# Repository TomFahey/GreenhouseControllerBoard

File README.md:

# Greenhouse Controller Board
Greenhouse irrigation control and sensor board, based on the ESP32 microcontroller and designed with Autodesk Eagle.

A simple 2-layer PCB design for an irrigation controller, designed to control up to four 12V solenoid valve water valves, 
based on temperature, humidity and other arbitrary parameters.

Based on Espressif's popular ESP32 microncontroller, this controller board incorporates a number of features, including:

- Flexible Wi-Fi/Bluetooth control, tracking and automation of plants through open-source Arduino libraries (also compatible with ESPHome)
- Individual control for up to four DC solenoid valves via 2.1mm x 5.5mm barrel jack, with LED status indicators
- 12V DC power input, built-in 3.3V voltage regulation for microcontroller and peripherals, up to 4A load
- High precision temperature, pressure and humidity sensing, using Bosch's BME280 MEMS sensor
- Up to 8 individual 12-bit ADC channels for additional environmental monitoring, such as soil moisture sensors
- An additional 4 GPIO channels, and two I2C connectors for further expansion e.g LED strips (separate power supply required)

Some renders from Fusion 360:

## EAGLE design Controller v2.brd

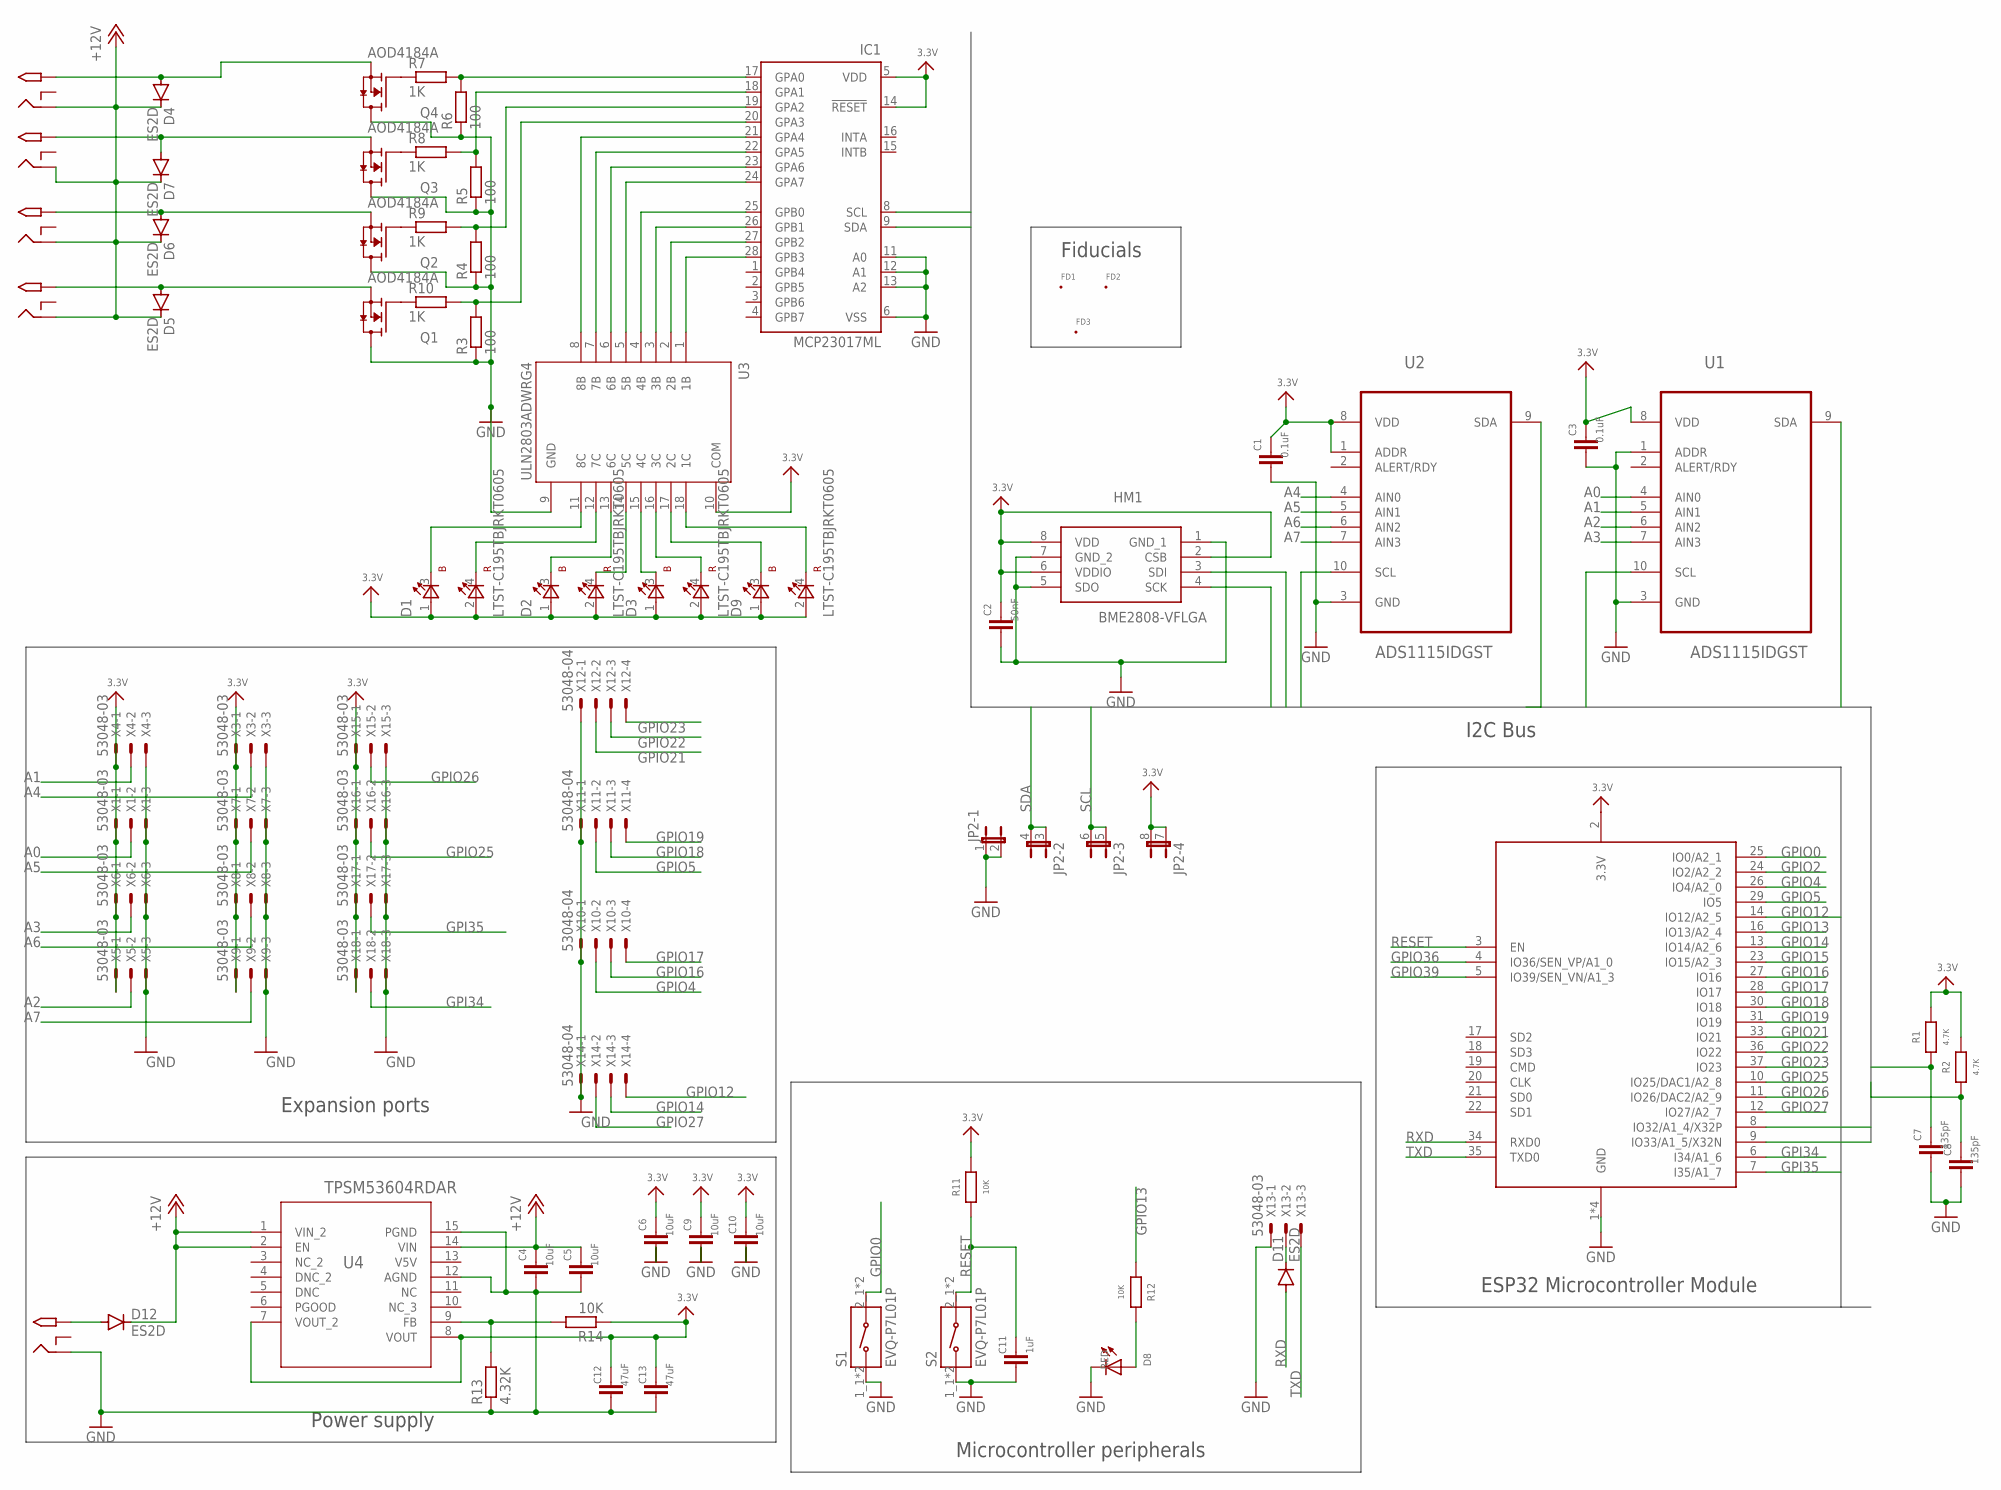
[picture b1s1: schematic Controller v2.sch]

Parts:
12V_OUT_A, 12V_OUT_B, 12V_OUT_C, 12V_OUT_D: 2.1MMJACKTHM; PJ-102A
C1, C3: 0.1uF; C0603
C2: 50nF; C0603
C4, C5, C6, C9, C10: 10uF; C0805K
C7, C8: 135pF; C0603
C11: 1uF; C0805K
C12, C13: 47uF; C0805K
D1, D2, D3, D9: LTST-C195TBJRKT0605; LED_LTST-C195TBJRKT
D4, D5, D6, D7, D11, D12: ES2D; SMB; MPN ES2D; DIGI-KEY-PART-NUMBER ES2DFSCT-ND
D8: RED; CHIPLED_0805
FD1, FD2, FD3: FID_20MIL; FID_020
HM1: BME2808-VFLGA; BME280
IC1: MCP23017ML; QFN28-ML_6X6MM
JP2: 3.3V; JP4Q
PWRIN: 2.1MMJACKTHM; PJ-102A
Q1, Q2, Q3, Q4: AOD4184A; D-PAK_TO252AA
R1, R2: 4.7K; R0805
R3, R4, R5, R6: 100; R0402
R7, R8, R9, R10: 1K; R0402
R11: 10K; R0603
R12: 10K; R0805
R13: 4.32K; R0402
R14: 10K; R0402
S1, S2: EVQ-P7L01P; SW_EVQ-P7L01P
U1, U2: ADS1115IDGST; SOP50P490X110-10N
U3: ULN2803ADWRG4; SOIC127P1030X265-18N
U4: TPSM53604RDAR; B3QFN14_RDA_TEX
X1, X3, X4, X5, X6, X7, X8, X9, X13, X15, X16, X17, X18: 53048-03
X2: ESP32_WROOM32; WROOM32; MPN N/A
X10, X11, X12, X14: 53048-04

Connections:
3.3V: C1.1, C2.1, C3.1, C6.1, C9.1, C10.1, C12.1, C13.1, D1.1 (A1), D1.2 (A2), D2.1 (A1), D2.2 (A2), D3.1 (A1), D3.2 (A2), D9.1 (A1), D9.2 (A2), HM1.2 (CSB), HM1.6 (VDDIO), HM1.8 (VDD), IC1.5 (VDD), IC1.14 (!RESET), JP2.7 (1), JP2.8 (2), R1.2, R2.2, R11.2, R14.1, U1.8 (VDD), U2.1 (ADDR), U2.8 (VDD), U3.10 (COM), U4.7 (VOUT_2), U4.8 (VOUT), X1.1, X2.2 (3.3V), X3.1, X4.1, X5.1, X6.1, X7.1, X8.1, X9.1, X15.1, X16.1, X17.1, X18.1
+12V: 12V_OUT_A.RING, 12V_OUT_B.RING, 12V_OUT_C.RING, 12V_OUT_D.RING, C4.1, C5.1, D4.C, D5.C, D6.C, D7.C, D12.C, U4.1 (VIN_2), U4.2 (EN), U4.14 (VIN)
A0: U1.4 (AIN0), X1.2
A1: U1.5 (AIN1), X4.2
A2: U1.6 (AIN2), X5.2
A3: U1.7 (AIN3), X6.2
A4: U2.4 (AIN0), X3.2
A5: U2.5 (AIN1), X7.2
A6: U2.6 (AIN2), X8.2
A7: U2.7 (AIN3), X9.2
GND: C1.2, C2.2, C3.2, C4.2, C5.2, C6.2, C7.2, C8.2, C9.2, C10.2, C11.2, C12.2, C13.2, D8.C, HM1.1 (GND_1), HM1.5 (SDO), HM1.7 (GND_2), IC1.6 (VSS), IC1.11 (A0), IC1.12 (A1), IC1.13 (A2), JP2.1, JP2.2, PWRIN.RING, Q1.4 (D), Q2.4 (D), Q3.4 (D), Q4.4 (D), R3.1, R4.1, R5.1, R6.1, R13.1, S1.1_1 (1), S1.1_2 (1), S2.1_1 (1), S2.1_2 (1), U1.1 (ADDR), U1.3 (GND), U2.3 (GND), U3.9 (GND), U4.12 (AGND), U4.15 (PGND), X1.3, X2.1 (GND), X2.15 (GND), X2.38 (GND), X2.P$1 (GND), X3.3, X4.3, X5.3, X6.3, X7.3, X8.3, X9.3, X10.1, X11.1, X12.1, X13.1, X14.1, X15.3, X16.3, X17.3, X18.3
GPI34: X2.6 (I34/A1_6), X18.2
GPI35: X2.7 (I35/A1_7), X17.2
GPIO0: S1.2_1 (2), S1.2_2 (2), X2.25 (IO0/A2_1)
GPIO2: X2.24 (IO2/A2_2)
GPIO4: X2.26 (IO4/A2_0), X10.2
GPIO5: X2.29 (IO5), X11.2
GPIO12: X2.14 (IO12/A2_5), X14.4
GPIO13: R12.1, X2.16 (IO13/A2_4)
GPIO14: X2.13 (IO14/A2_6), X14.3
GPIO15: X2.23 (IO15/A2_3)
GPIO16: X2.27 (IO16), X10.3
GPIO17: X2.28 (IO17), X10.4
GPIO18: X2.30 (IO18), X11.3
GPIO19: X2.31 (IO19), X11.4
GPIO21: X2.33 (IO21), X12.2
GPIO22: X2.36 (IO22), X12.3
GPIO23: X2.37 (IO23), X12.4
GPIO25: X2.10 (IO25/DAC1/A2_8), X16.2
GPIO26: X2.11 (IO26/DAC2/A2_9), X15.2
GPIO27: X2.12 (IO27/A2_7), X14.2
GPIO36: X2.4 (IO36/SEN_VP/A1_0)
GPIO39: X2.5 (IO39/SEN_VN/A1_3)
unnamed: IC1.17 (GPA0), R6.2, R7.2
unnamed: IC1.18 (GPA1), R5.2, R8.2
unnamed: IC1.20 (GPA3), R3.2, R10.2
unnamed: IC1.19 (GPA2), R4.2, R9.2
unnamed: Q1.1 (G), R10.1
unnamed: D12.A, PWRIN.TIP
unnamed: Q2.1 (G), R9.1
unnamed: IC1.21 (GPA4), U3.8 (8B)
unnamed: Q3.1 (G), R8.1
unnamed: Q4.1 (G), R7.1
unnamed: D11.C, X13.2
unnamed: IC1.22 (GPA5), U3.7 (7B)
unnamed: IC1.23 (GPA6), U3.6 (6B)
unnamed: IC1.24 (GPA7), U3.5 (5B)
unnamed: D8.A, R12.2
unnamed: IC1.25 (GPB0), U3.4 (4B)
unnamed: IC1.26 (GPB1), U3.3 (3B)
unnamed: IC1.27 (GPB2), U3.2 (2B)
unnamed: IC1.28 (GPB3), U3.1 (1B)
unnamed: D1.3 (K1), U3.11 (8C)
unnamed: D1.4 (K2), U3.12 (7C)
unnamed: D2.3 (K1), U3.13 (6C)
unnamed: D2.4 (K2), U3.14 (5C)
unnamed: D3.3 (K1), U3.15 (4C)
unnamed: D3.4 (K2), U3.16 (3C)
unnamed: D9.3 (K1), U3.17 (2C)
unnamed: D9.4 (K2), U3.18 (1C)
unnamed: R13.2, R14.2, U4.9 (FB)
RESET: C11.1, R11.1, S2.2_1 (2), S2.2_2 (2), X2.3 (EN)
RXD: D11.A, X2.34 (RXD0)
SCL: C7.1, HM1.4 (SCK), IC1.8 (SCL), JP2.5 (1), JP2.6 (2), R1.1, U1.10 (SCL), U2.10 (SCL), X2.9 (IO33/A1_5/X32N)
SDA: C8.1, HM1.3 (SDI), IC1.9 (SDA), JP2.3 (1), JP2.4 (2), R2.1, U1.9 (SDA), U2.9 (SDA), X2.8 (IO32/A1_4/X32P)
TXD: X2.35 (TXD0), X13.3
V_COL1: 12V_OUT_A.TIP, D4.A, Q4.3 (S)
V_COL2: 12V_OUT_B.TIP, D7.A, Q3.3 (S)
V_COL3: 12V_OUT_C.TIP, D6.A, Q2.3 (S)
V_COL4: 12V_OUT_D.TIP, D5.A, Q1.3 (S)

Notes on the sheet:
Fiducials
I2C Bus
Microcontroller peripherals
ESP32 Microcontroller Module
Power supply
Expansion ports

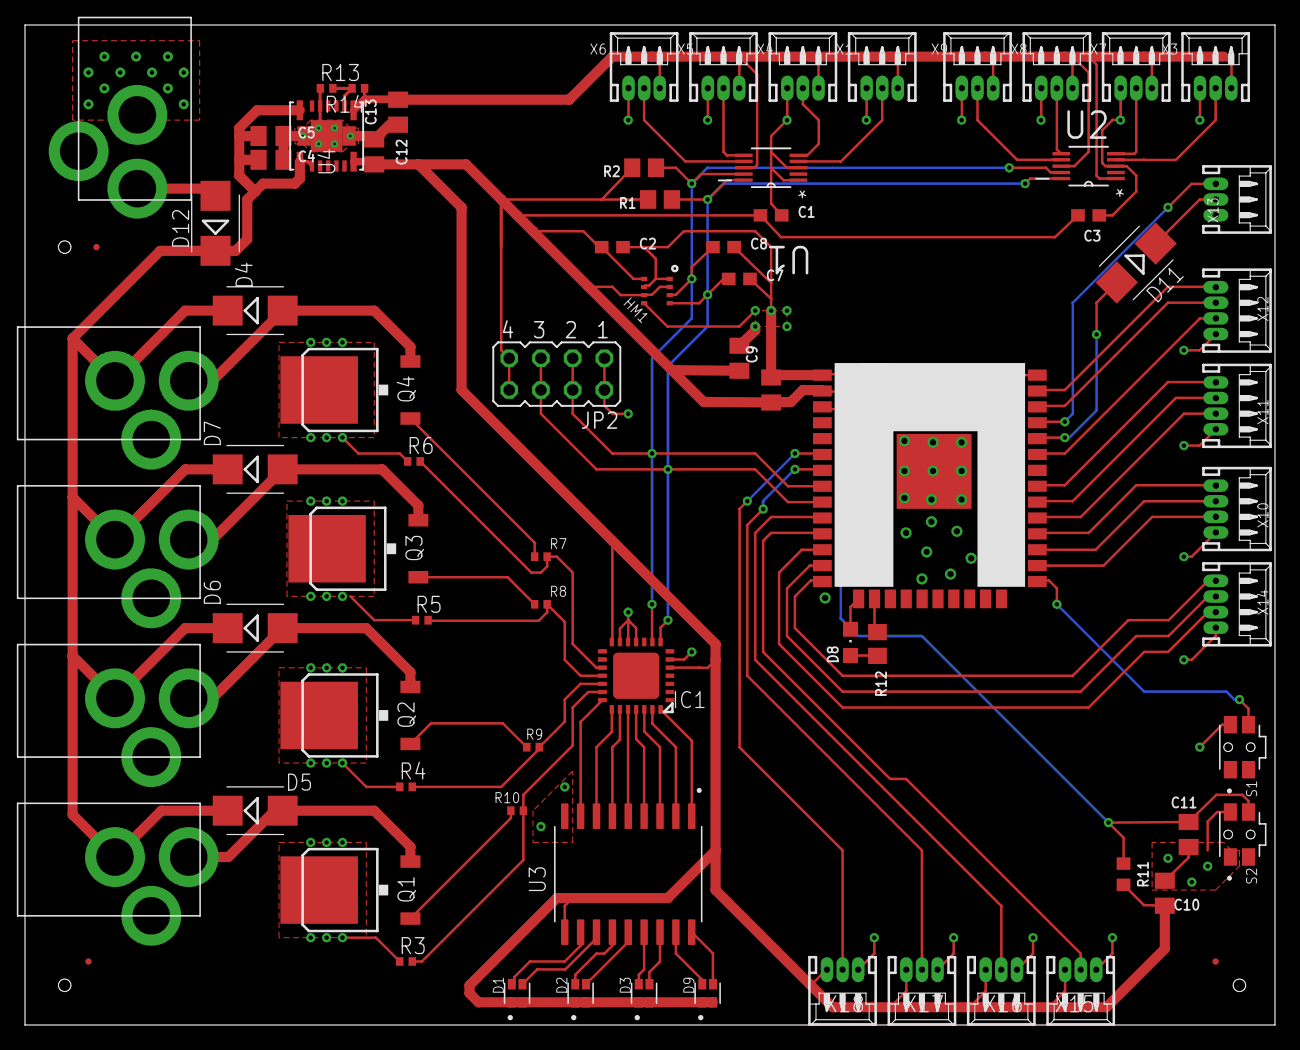
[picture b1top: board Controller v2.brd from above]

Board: 2 copper layers, 100.0 x 80.0 mm, 77 parts (0 on the bottom side), 66 nets.

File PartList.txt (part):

Partlist

Exported from Controller v2.sch at 12/07/2021 17:28

EAGLE Version 9.6.2 Copyright (c) 1988-2020 Autodesk, Inc.

Assembly variant: 

Part      Value               Device              Package              Library                                Sheet

12V_OUT_A 2.1MMJACKTHM        2.1MMJACKTHM        PJ-102A              adafruit                               1
12V_OUT_B 2.1MMJACKTHM        2.1MMJACKTHM        PJ-102A              adafruit                               1
12V_OUT_C 2.1MMJACKTHM        2.1MMJACKTHM        PJ-102A              adafruit                               1
12V_OUT_D 2.1MMJACKTHM        2.1MMJACKTHM        PJ-102A              adafruit                               1
C1        0.1uF               C-EUC0603           C0603                rcl                                    1
C2        50nF                C-EUC0603           C0603                rcl                                    1
C3        0.1uF               C-EUC0603           C0603                rcl                                    1
C4        10uF                C-EUC0805K          C0805K               rcl                                    1
C5        10uF                C-EUC0805K          C0805K               rcl                                    1
C6        10uF                C-EUC0805K          C0805K               rcl                                    1
C7        135pF               C-EUC0603           C0603                rcl                                    1
C8        135pF               C-EUC0603           C0603                rcl                                    1
C9        10uF                C-EUC0805K          C0805K               rcl                                    1
C10       10uF                C-EUC0805K          C0805K               rcl                                    1
C11       1uF                 C-EUC0805K          C0805K               rcl                                    1
C12       47uF                C-EUC0805K          C0805K               rcl                                    1
C13       47uF                C-EUC0805K          C0805K               rcl                                    1
D1        LTST-C195TBJRKT0605 LTST-C195TBJRKT0605 LED_LTST-C195TBJRKT  LTST-C195TBJRKT                        1
D2        LTST-C195TBJRKT0605 LTST-C195TBJRKT0605 LED_LTST-C195TBJRKT  LTST-C195TBJRKT                        1
D3        LTST-C195TBJRKT0605 LTST-C195TBJRKT0605 LED_LTST-C195TBJRKT  LTST-C195TBJRKT                        1
D4        ES2D                ES2D                SMB                  diode                                  1
D5        ES2D                ES2D                SMB                  diode                                  1
D6        ES2D                ES2D                SMB                  diode                                  1
D7        ES2D                ES2D                SMB                  diode                                  1
D8        RED                 LEDCHIPLED_0805     CHIPLED_0805         adafruit                               1
D9        LTST-C195TBJRKT0605 LTST-C195TBJRKT0605 LED_LTST-C195TBJRKT  LTST-C195TBJRKT                        1
D11       ES2D                ES2D                SMB                  diode                                  1
D12       ES2D                ES2D                SMB                  diode                                  1
HM1       BME2808-VFLGA       BME2808-VFLGA       BME280               SamacSys_Parts                         1
IC1       MCP23017ML          MCP23017ML          QFN28-ML_6X6MM       microchip                              1
JP2       3.3V                JP4QE               JP4Q                 jumper                                 1
PWRIN     2.1MMJACKTHM        2.1MMJACKTHM        PJ-102A              adafruit                               1
Q1        AOD4184A            AOD4184A            D-PAK_TO252AA        AOD4184A                               1
Q2        AOD4184A            AOD4184A            D-PAK_TO252AA        AOD4184A                               1
Q3        AOD4184A            AOD4184A            D-PAK_TO252AA        AOD4184A                               1
Q4        AOD4184A            AOD4184A            D-PAK_TO252AA        AOD4184A                               1
R1        4.7K                R-EU_R0805          R0805                rcl                                    1
R2        4.7K                R-EU_R0805          R0805                rcl                                    1
R3        100                 R-EU_R0402          R0402                rcl                                    1
R4        100                 R-EU_R0402          R0402                rcl                                    1
R5        100                 R-EU_R0402          R0402                rcl                                    1
R6        100                 R-EU_R0402          R0402                rcl                                    1
R7        1K                  R-EU_R0402          R0402                rcl                                    1
R8        1K                  R-EU_R0402          R0402                rcl                                    1
R9        1K                  R-EU_R0402          R0402                rcl                                    1
R10       1K                  R-EU_R0402          R0402                rcl                                    1
R11       10K                 R-EU_R0603          R0603                rcl                                    1
R12       10K                 R-EU_R0805          R0805                rcl                                    1
R13       4.32K               R-EU_R0402          R0402                rcl                                    1
R14       10K                 R-EU_R0402          R0402                rcl                                    1
S1        EVQ-P7L01P          EVQ-P7L01P          SW_EVQ-P7L01P        EVQ-P7L01P                             1
S2        EVQ-P7L01P          EVQ-P7L01P          SW_EVQ-P7L01P        EVQ-P7L01P                             1
U1        ADS1115IDGST        ADS1115IDGST        SOP50P490X110-10N    Texas Instruments_By_element14_Batch_1 1
U2        ADS1115IDGST        ADS1115IDGST        SOP50P490X110-10N    Texas Instruments_By_element14_Batch_1 1
U3        ULN2803ADWRG4       ULN2803ADWRG4       SOIC127P1030X265-18N ULN2803ADWRG4                          1
U4        TPSM53604RDAR       TPSM53604RDAR       B3QFN14_RDA_TEX      TPSM53604                              1
X1        53048-03            53048-03            53048-03             con-molex                              1
X2        ESP32_WROOM32       ESP32_WROOM32       WROOM32              microbuilder                           1
X3        53048-03            53048-03            53048-03             con-molex                              1
X4        53048-03            53048-03            53048-03             con-molex                              1
X5        53048-03            53048-03            53048-03             con-molex                              1
X6        53048-03            53048-03            53048-03             con-molex                              1
X7        53048-03            53048-03            53048-03             con-molex                              1
X8        53048-03            53048-03            53048-03             con-molex                              1
X9        53048-03            53048-03            53048-03             con-molex                              1
X10       53048-04            53048-04            53048-04             con-molex                              1
X11       53048-04            53048-04            53048-04             con-molex                              1
X12       53048-04            53048-04            53048-04             con-molex                              1
X13       53048-03            53048-03            53048-03             con-molex                              1
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
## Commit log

2021-07-12 Initial draft README
2021-07-12 Updated board
2021-07-12 Added some pictures
2021-07-12 Added part list

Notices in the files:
parts and their libraries:
microbuilder: This work is placed in the public domain, and may be freely used for commercial and non-commercial work with the following conditions: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
COPYRIGHT: Copyright (C) 2018 Accelerated Designs. All rights reserved
